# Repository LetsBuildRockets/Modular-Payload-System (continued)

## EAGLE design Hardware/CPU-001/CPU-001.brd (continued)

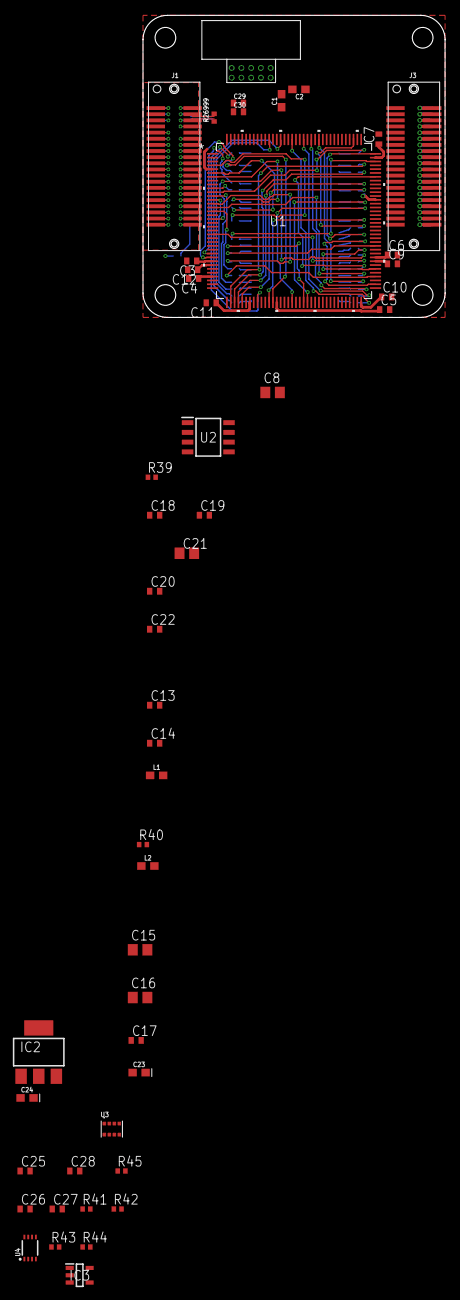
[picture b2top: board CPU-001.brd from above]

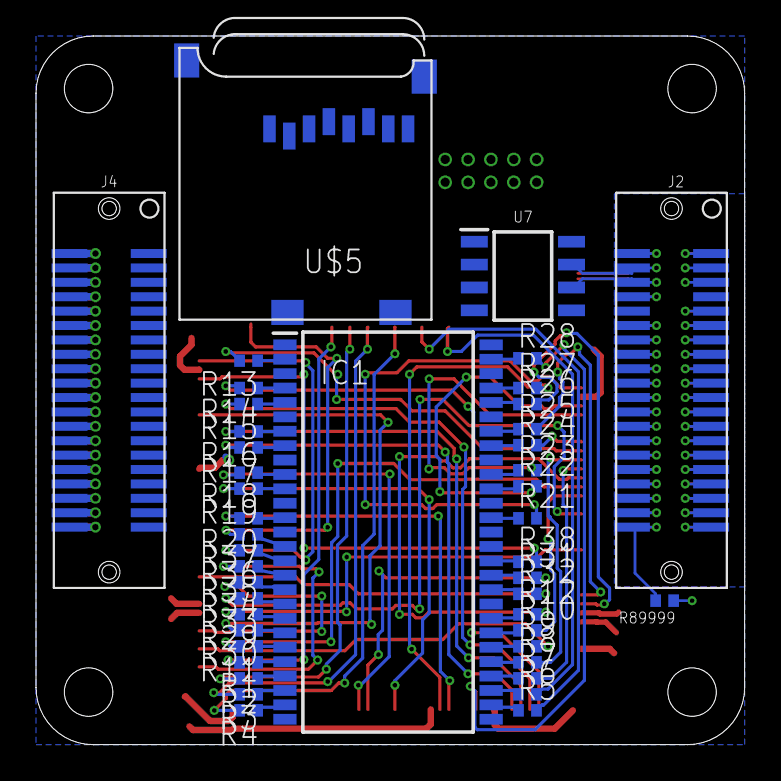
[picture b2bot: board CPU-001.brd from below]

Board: 2 copper layers, 39.4 x 39.4 mm, 93 parts (44 on the bottom side), 135 nets.

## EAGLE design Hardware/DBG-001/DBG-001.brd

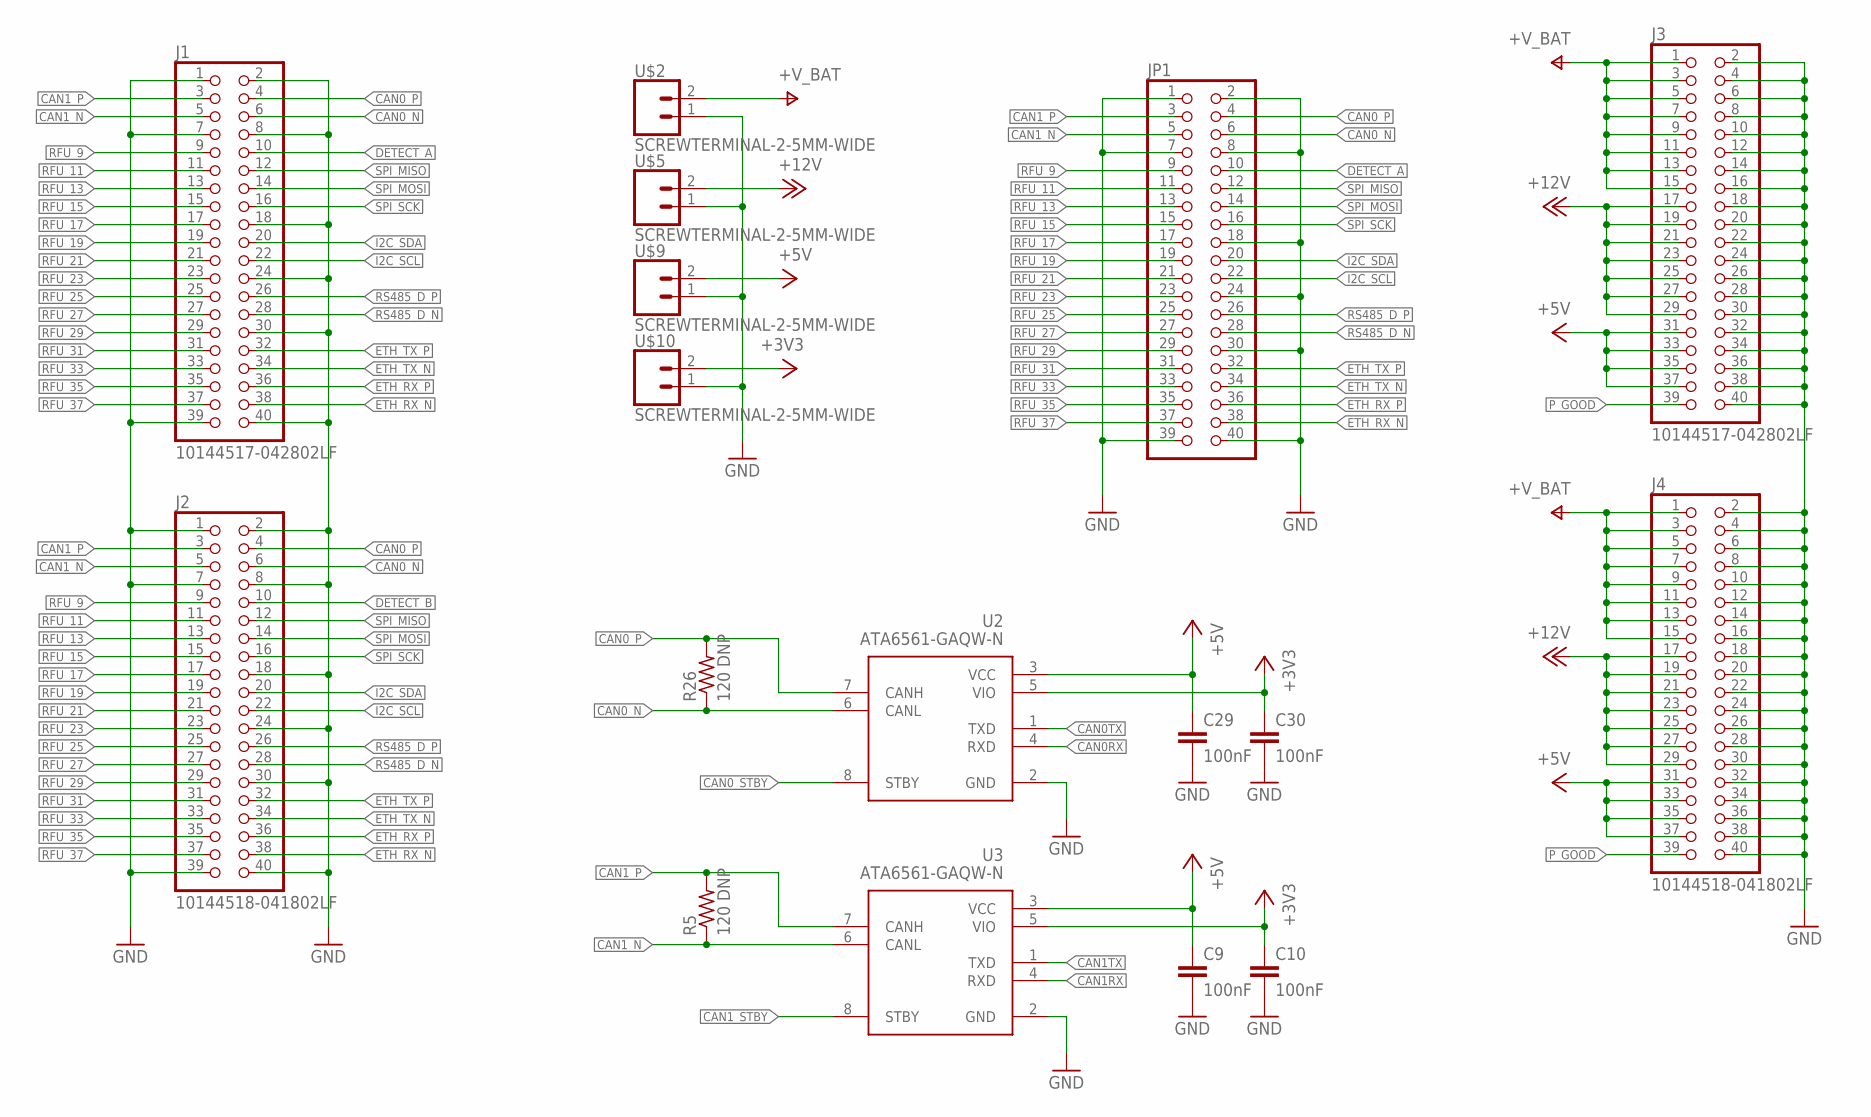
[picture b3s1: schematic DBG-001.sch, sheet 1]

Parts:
C9, C10, C29, C30: 100nF; C0402
J1, J3: 10144517-042802LF
J2, J4: 10144518-041802LF
JP1: PINHD-2X20; 2X20
R5, R26: 120 DNP; R0402
U2, U3: ATA6561-GAQW-N; SOIC127P600X175-8N
U$2, U$5, U$9, U$10: SCREWTERMINAL-2-5MM-WIDE; SCREWTERMINAL-5MM-2-WIDE

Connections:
+3V3: C10.1, C30.1, U2.5 (VIO), U3.5 (VIO), U$10.2; also elsewhere on the board
+5V: C9.1, C29.1, J3.31, J3.33, J3.35, J3.37, J4.31, J4.33, J4.35, J4.37, U2.3 (VCC), U3.3 (VCC), U$9.2; also elsewhere on the board
+12V: J3.17, J3.19, J3.21, J3.23, J3.25, J3.27, J3.29, J4.17, J4.19, J4.21, J4.23, J4.25, J4.27, J4.29, U$5.2
+V_BAT: J3.1, J3.3, J3.5, J3.7, J3.9, J3.11, J3.13, J3.15, J4.1, J4.3, J4.5, J4.7, J4.9, J4.11, J4.13, J4.15, U$2.2
CAN0RX: U2.4 (RXD); also elsewhere on the board
CAN0TX: U2.1 (TXD); also elsewhere on the board
CAN0_N: J1.6, J2.6, JP1.6, R26.1, U2.6 (CANL)
CAN0_P: J1.4, J2.4, JP1.4, R26.2, U2.7 (CANH)
CAN0_STBY: U2.8 (STBY); also elsewhere on the board
CAN1RX: U3.4 (RXD); also elsewhere on the board
CAN1TX: U3.1 (TXD); also elsewhere on the board
CAN1_N: J1.5, J2.5, JP1.5, R5.1, U3.6 (CANL)
CAN1_P: J1.3, J2.3, JP1.3, R5.2, U3.7 (CANH)
CAN1_STBY: U3.8 (STBY); also elsewhere on the board
DETECT_A: J1.10, JP1.10; also elsewhere on the board
DETECT_B: J2.10; also elsewhere on the board
ETH_RX_N: J1.38, J2.38, JP1.38
ETH_RX_P: J1.36, J2.36, JP1.36
ETH_TX_N: J1.34, J2.34, JP1.34
ETH_TX_P: J1.32, J2.32, JP1.32
GND: C9.2, C10.2, C29.2, C30.2, J1.1, J1.2, J1.7, J1.8, J1.18, J1.24, J1.30, J1.39, J1.40, J2.1, J2.2, J2.7, J2.8, J2.18, J2.24, J2.30, J2.39, J2.40, J3.2, J3.4, J3.6, J3.8, J3.10, J3.12, J3.14, J3.16, J3.18, J3.20, J3.22, J3.24, J3.26, J3.28, J3.30, J3.32, J3.34, J3.36, J3.38, J3.40, J4.2, J4.4, J4.6, J4.8, J4.10, J4.12, J4.14, J4.16, J4.18, J4.20, J4.22, J4.24, J4.26, J4.28, J4.30, J4.32, J4.34, J4.36, J4.38, J4.40, JP1.1, JP1.2, JP1.7, JP1.8, JP1.18, JP1.24, JP1.30, JP1.39, JP1.40, U2.2 (GND), U3.2 (GND), U$2.1, U$5.1, U$9.1, U$10.1; also elsewhere on the board
I2C_SCL: J1.22, J2.22, JP1.22; also elsewhere on the board
I2C_SDA: J1.20, J2.20, JP1.20; also elsewhere on the board
P_GOOD: J3.39, J4.39; also elsewhere on the board
RFU_9: J1.9, J2.9, JP1.9
RFU_11: J1.11, J2.11, JP1.11
RFU_13: J1.13, J2.13, JP1.13
RFU_15: J1.15, J2.15, JP1.15
RFU_17: J1.17, J2.17, JP1.17
RFU_19: J1.19, J2.19, JP1.19
RFU_21: J1.21, J2.21, JP1.21
RFU_23: J1.23, J2.23, JP1.23
RFU_25: J1.25, J2.25, JP1.25
RFU_27: J1.27, J2.27, JP1.27
RFU_29: J1.29, J2.29, JP1.29
RFU_31: J1.31, J2.31, JP1.31
RFU_33: J1.33, J2.33, JP1.33
RFU_35: J1.35, J2.35, JP1.35
RFU_37: J1.37, J2.37, JP1.37
RS485_D_N: J1.28, J2.28, JP1.28
RS485_D_P: J1.26, J2.26, JP1.26
SPI_MISO: J1.12, J2.12, JP1.12; also elsewhere on the board
SPI_MOSI: J1.14, J2.14, JP1.14; also elsewhere on the board
SPI_SCK: J1.16, J2.16, JP1.16; also elsewhere on the board

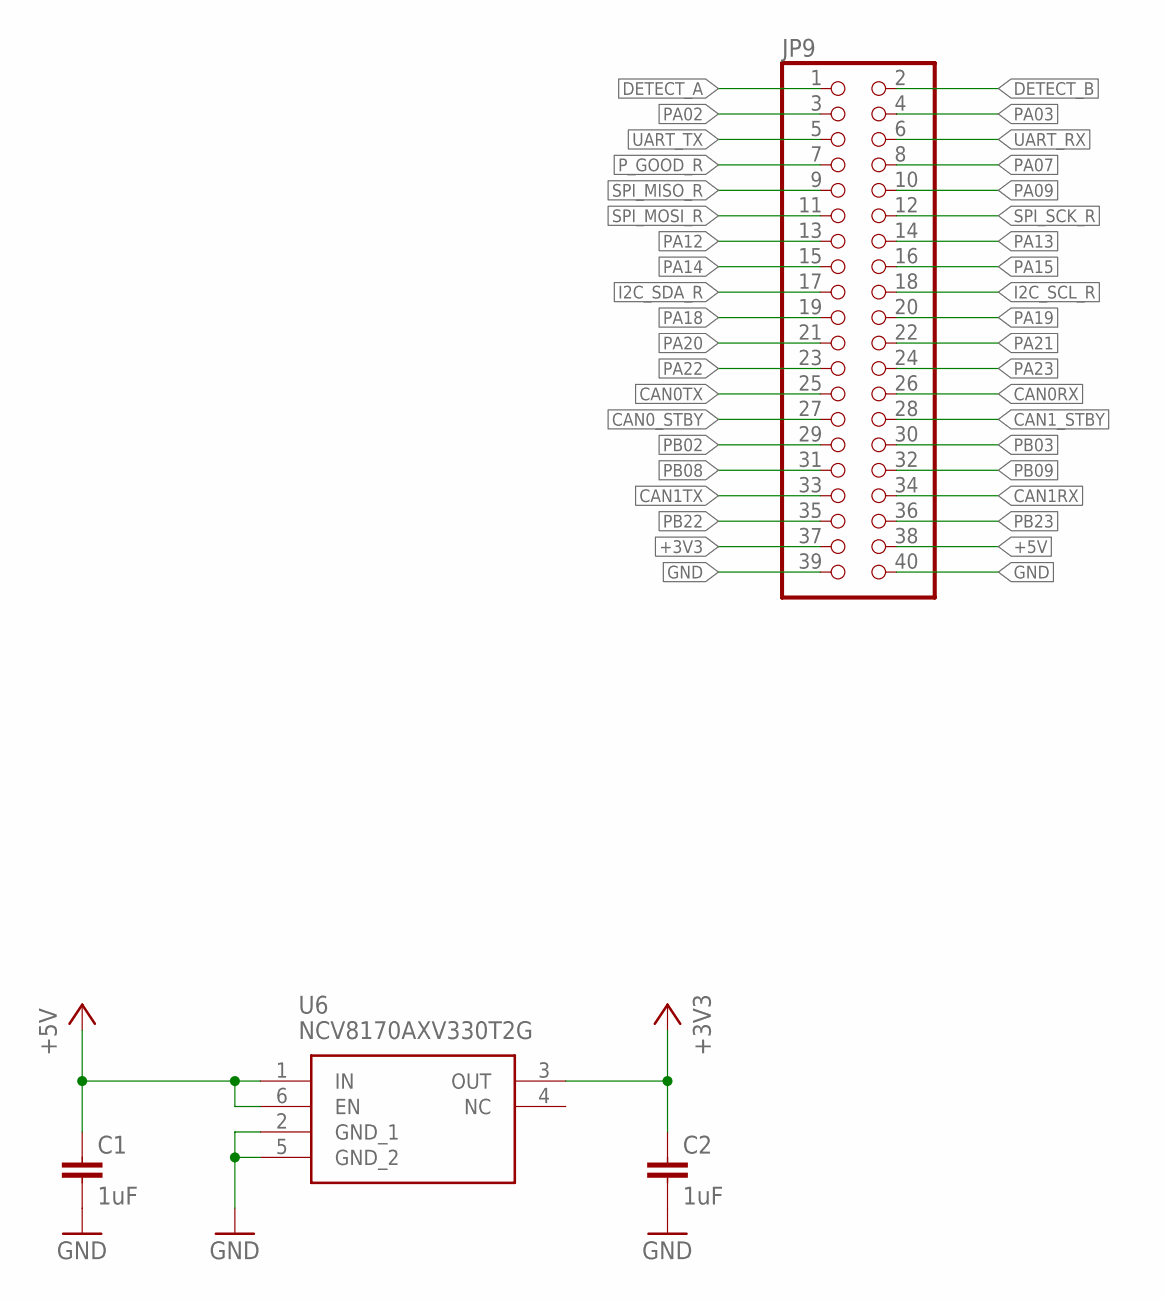
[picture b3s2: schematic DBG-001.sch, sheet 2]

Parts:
C1, C2: 1uF; C0603
JP9: PINHD-2X20; 2X20
U6: NCV8170AXV330T2G; SOTFL50P160X60-6N

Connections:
+3V3: C2.1, JP9.37, U6.3 (OUT); also elsewhere on the board
+5V: C1.1, JP9.38, U6.1 (IN), U6.6 (EN); also elsewhere on the board
CAN0RX: JP9.26; also elsewhere on the board
CAN0TX: JP9.25; also elsewhere on the board
CAN0_STBY: JP9.27; also elsewhere on the board
CAN1RX: JP9.34; also elsewhere on the board
CAN1TX: JP9.33; also elsewhere on the board
CAN1_STBY: JP9.28; also elsewhere on the board
DETECT_A: JP9.1; also elsewhere on the board
DETECT_B: JP9.2; also elsewhere on the board
GND: C1.2, C2.2, JP9.39, JP9.40, U6.2 (GND_1), U6.5 (GND_2); also elsewhere on the board
I2C_SCL_R: JP9.18; also elsewhere on the board
I2C_SDA_R: JP9.17; also elsewhere on the board
PA02: JP9.3; also elsewhere on the board
PA03: JP9.4; also elsewhere on the board
PA07: JP9.8; also elsewhere on the board
PA09: JP9.10; also elsewhere on the board
PA12: JP9.13; also elsewhere on the board
PA13: JP9.14; also elsewhere on the board
PA14: JP9.15; also elsewhere on the board
PA15: JP9.16; also elsewhere on the board
PA18: JP9.19; also elsewhere on the board
PA19: JP9.20; also elsewhere on the board
PA20: JP9.21; also elsewhere on the board
PA21: JP9.22; also elsewhere on the board
PA22: JP9.23; also elsewhere on the board
PA23: JP9.24; also elsewhere on the board
PB02: JP9.29; also elsewhere on the board
PB03: JP9.30; also elsewhere on the board
PB08: JP9.31; also elsewhere on the board
PB09: JP9.32; also elsewhere on the board
PB22: JP9.35; also elsewhere on the board
PB23: JP9.36; also elsewhere on the board
P_GOOD_R: JP9.7; also elsewhere on the board
SPI_MISO_R: JP9.9; also elsewhere on the board
SPI_MOSI_R: JP9.11; also elsewhere on the board
SPI_SCK_R: JP9.12; also elsewhere on the board
UART_RX: JP9.6; also elsewhere on the board
UART_TX: JP9.5; also elsewhere on the board

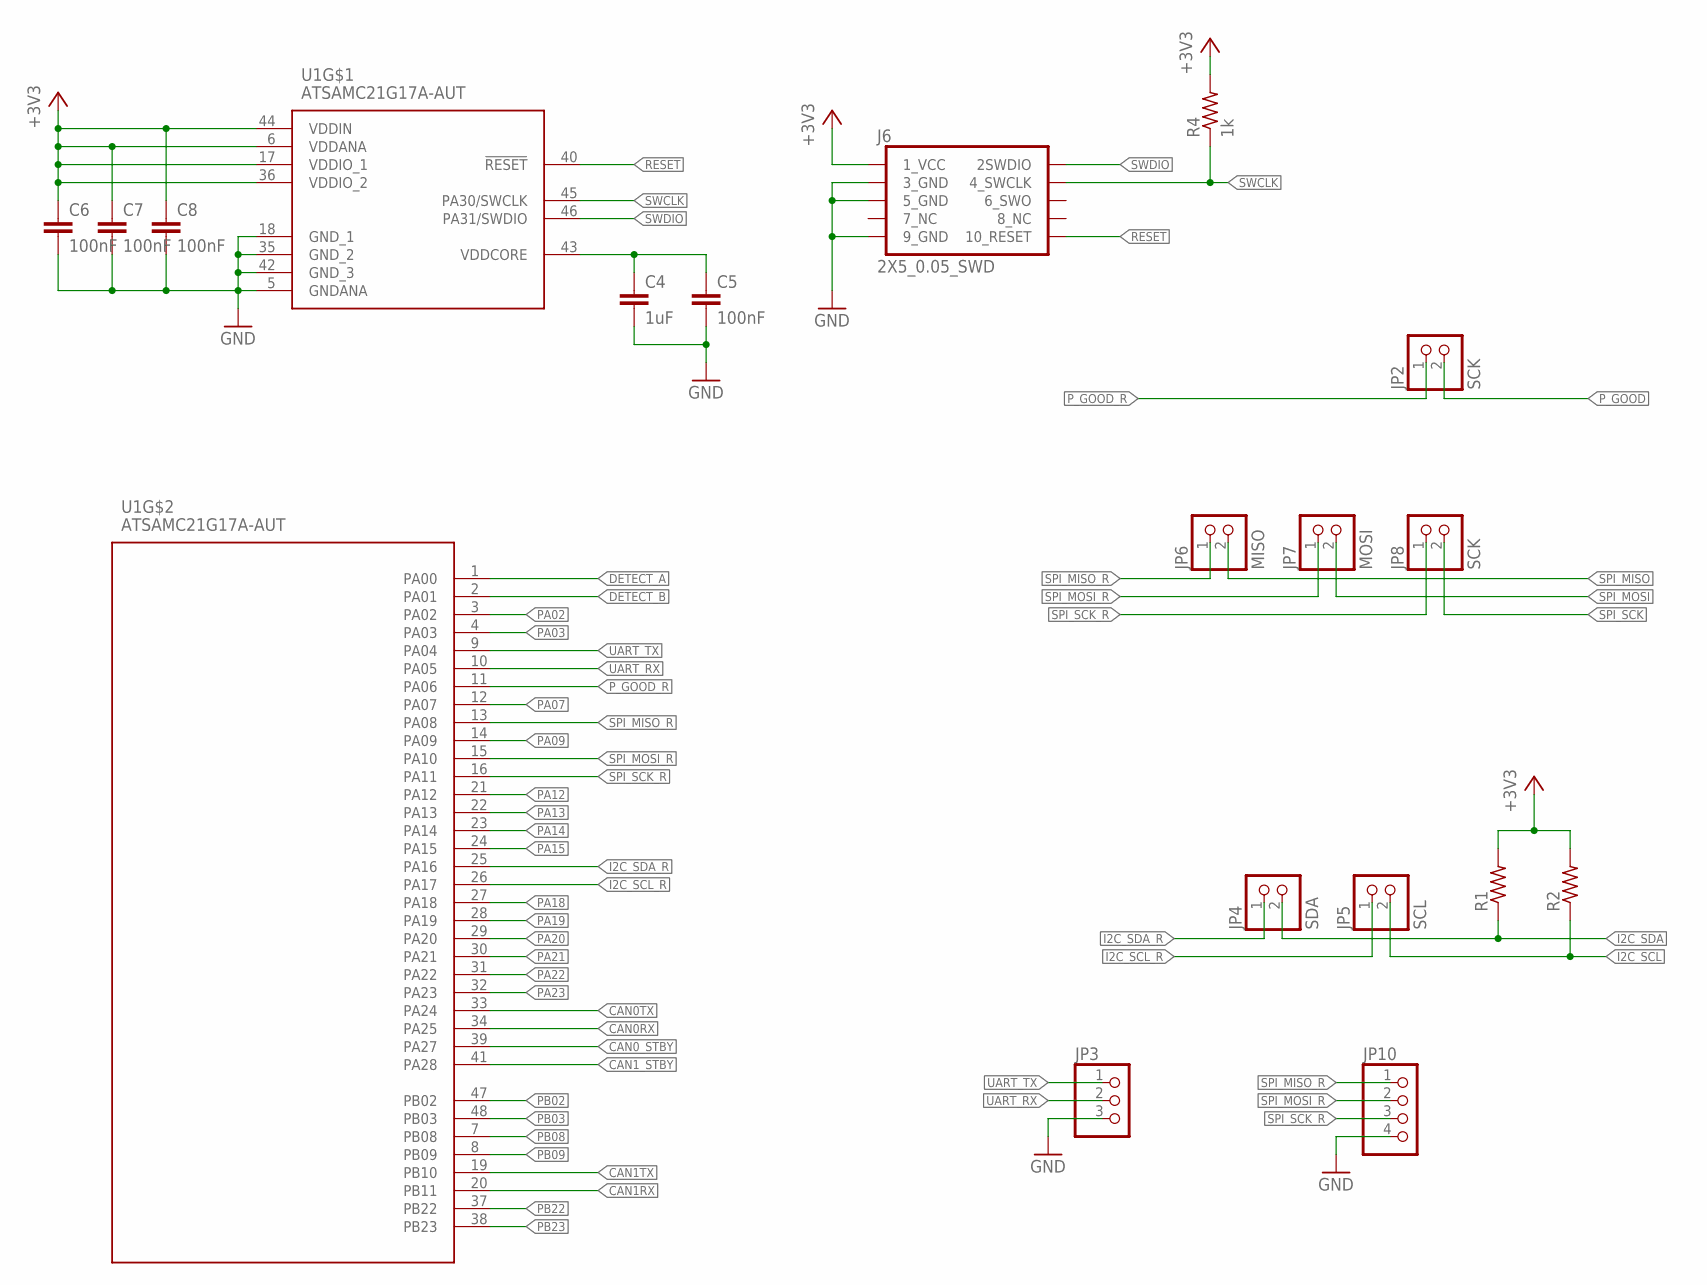
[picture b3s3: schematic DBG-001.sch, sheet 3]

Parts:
C4: 1uF; C0805
C5, C6, C7, C8: 100nF; C0805
J6: 2X5_0.05_SWD; 2X5_RIGHT
JP2, JP8: SCK; 1X02
JP3: PINHD-1X3; 1X03
JP4: SDA; 1X02
JP5: SCL; 1X02
JP6: MISO; 1X02
JP7: MOSI; 1X02
JP10: PINHD-1X4; 1X04
R1, R2: R-US_R0805; R0805
R4: 1k; R0402
U1: ATSAMC21G17A-AUT; QFP50P900X900X120-48N

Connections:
+3V3: C6.1, C7.1, C8.1, J6.1 (1_VCC), R1.2, R2.2, R4.2, U1.6 (VDDANA), U1.17 (VDDIO_1), U1.36 (VDDIO_2), U1.44 (VDDIN); also elsewhere on the board
CAN0RX: U1.34 (PA25); also elsewhere on the board
CAN0TX: U1.33 (PA24); also elsewhere on the board
CAN0_STBY: U1.39 (PA27); also elsewhere on the board
CAN1RX: U1.20 (PB11); also elsewhere on the board
CAN1TX: U1.19 (PB10); also elsewhere on the board
CAN1_STBY: U1.41 (PA28); also elsewhere on the board
DETECT_A: U1.1 (PA00); also elsewhere on the board
DETECT_B: U1.2 (PA01); also elsewhere on the board
GND: C4.2, C5.2, C6.2, C7.2, C8.2, J6.3 (3_GND), J6.5 (5_GND), J6.9 (9_GND), JP3.3, JP10.4, U1.5 (GNDANA), U1.18 (GND_1), U1.35 (GND_2), U1.42 (GND_3); also elsewhere on the board
I2C_SCL: JP5.2, R2.1; also elsewhere on the board
I2C_SCL_R: JP5.1, U1.26 (PA17); also elsewhere on the board
I2C_SDA: JP4.2, R1.1; also elsewhere on the board
I2C_SDA_R: JP4.1, U1.25 (PA16); also elsewhere on the board
unnamed: C4.1, C5.1, U1.43 (VDDCORE)
PA02: U1.3 (PA02); also elsewhere on the board
PA03: U1.4 (PA03); also elsewhere on the board
PA07: U1.12 (PA07); also elsewhere on the board
PA09: U1.14 (PA09); also elsewhere on the board
PA12: U1.21 (PA12); also elsewhere on the board
PA13: U1.22 (PA13); also elsewhere on the board
PA14: U1.23 (PA14); also elsewhere on the board
PA15: U1.24 (PA15); also elsewhere on the board
PA18: U1.27 (PA18); also elsewhere on the board
PA19: U1.28 (PA19); also elsewhere on the board
PA20: U1.29 (PA20); also elsewhere on the board
PA21: U1.30 (PA21); also elsewhere on the board
PA22: U1.31 (PA22); also elsewhere on the board
PA23: U1.32 (PA23); also elsewhere on the board
PB02: U1.47 (PB02); also elsewhere on the board
PB03: U1.48 (PB03); also elsewhere on the board
PB08: U1.7 (PB08); also elsewhere on the board
PB09: U1.8 (PB09); also elsewhere on the board
PB22: U1.37 (PB22); also elsewhere on the board
PB23: U1.38 (PB23); also elsewhere on the board
P_GOOD: JP2.2; also elsewhere on the board
P_GOOD_R: JP2.1, U1.11 (PA06); also elsewhere on the board
RESET: J6.10 (10_RESET), U1.40 (!RESET)
SPI_MISO: JP6.2; also elsewhere on the board
SPI_MISO_R: JP6.1, JP10.1, U1.13 (PA08); also elsewhere on the board
SPI_MOSI: JP7.2; also elsewhere on the board
SPI_MOSI_R: JP7.1, JP10.2, U1.15 (PA10); also elsewhere on the board
SPI_SCK: JP8.2; also elsewhere on the board
SPI_SCK_R: JP8.1, JP10.3, U1.16 (PA11); also elsewhere on the board
SWCLK: J6.4 (4_SWCLK), R4.1, U1.45 (PA30/SWCLK)
SWDIO: J6.2 (2SWDIO), U1.46 (PA31/SWDIO)
UART_RX: JP3.2, U1.10 (PA05); also elsewhere on the board
UART_TX: JP3.1, U1.9 (PA04); also elsewhere on the board

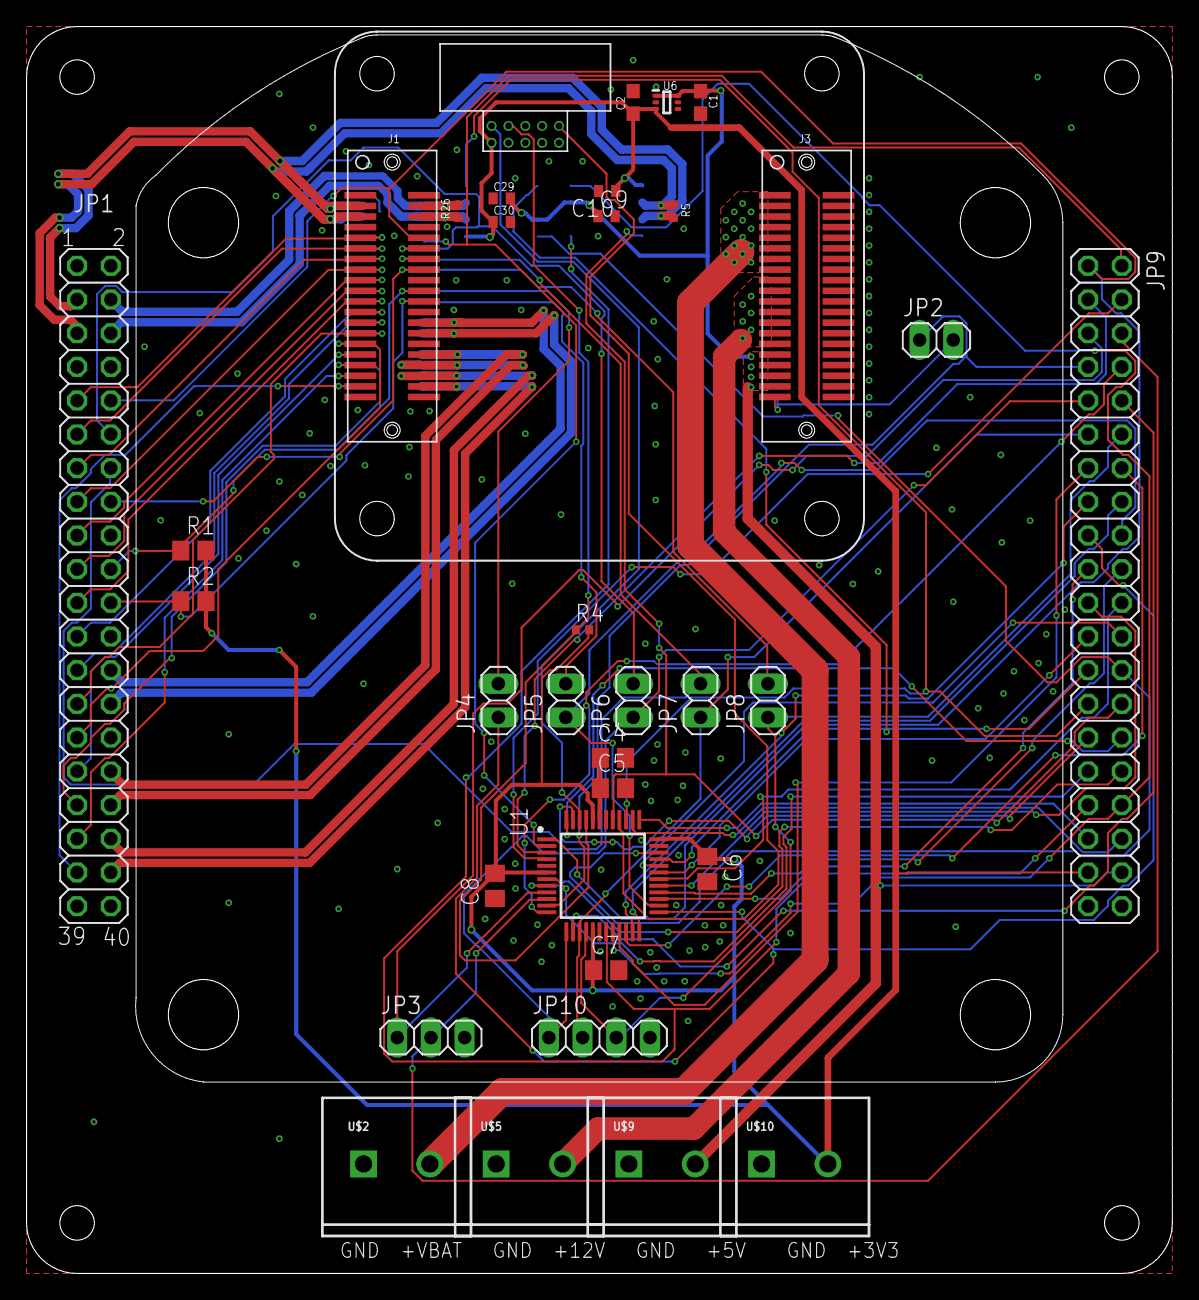
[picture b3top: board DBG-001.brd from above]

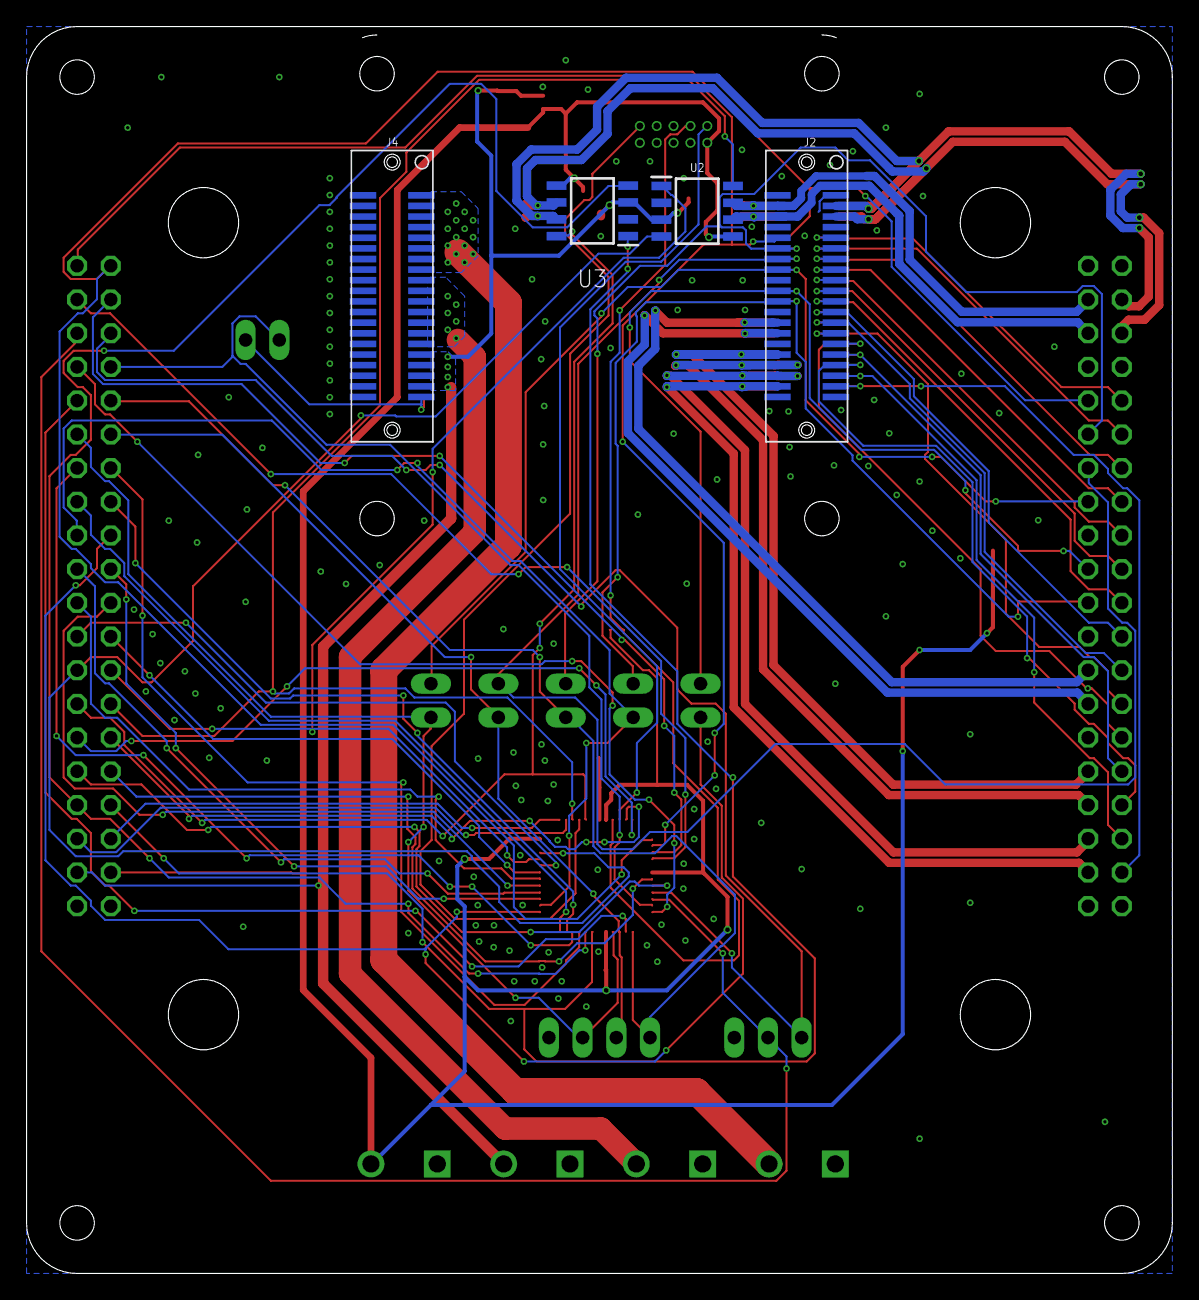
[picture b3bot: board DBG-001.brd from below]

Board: 2 copper layers, 86.4 x 94.0 mm, 39 parts (4 on the bottom side), 76 nets.

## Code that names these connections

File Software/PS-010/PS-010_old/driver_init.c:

/*
 * Code generated from Atmel Start.
 *
 * This file will be overwritten when reconfiguring your Atmel Start project.
 * Please copy examples or other code you want to keep to a separate file
 * to avoid losing it when reconfiguring.
 */

#include "driver_init.h"
#include <peripheral_clk_config.h>
#include <utils.h>
#include <hal_init.h>

#include <hpl_adc_base.h>

struct can_async_descriptor CAN_0;

struct adc_sync_descriptor ADC_0;

struct usart_sync_descriptor DEBUG_UART;

void ADC_0_PORT_init(void)
{

	// Disable digital pin circuitry
	gpio_set_pin_direction(PA02, GPIO_DIRECTION_OFF);

	gpio_set_pin_function(PA02, PINMUX_PA02B_ADC0_AIN0);

	// Disable digital pin circuitry
	gpio_set_pin_direction(PA04, GPIO_DIRECTION_OFF);

	gpio_set_pin_function(PA04, PINMUX_PA04B_ADC0_AIN4);

	// Disable digital pin circuitry
	gpio_set_pin_direction(PA05, GPIO_DIRECTION_OFF);

	gpio_set_pin_function(PA05, PINMUX_PA05B_ADC0_AIN5);

	// Disable digital pin circuitry
	gpio_set_pin_direction(PA06, GPIO_DIRECTION_OFF);

	gpio_set_pin_function(PA06, PINMUX_PA06B_ADC0_AIN6);

	// Disable digital pin circuitry
	gpio_set_pin_direction(PA07, GPIO_DIRECTION_OFF);

	gpio_set_pin_function(PA07, PINMUX_PA07B_ADC0_AIN7);

	// Disable digital pin circuitry
	gpio_set_pin_direction(PA08, GPIO_DIRECTION_OFF);

	gpio_set_pin_function(PA08, PINMUX_PA08B_ADC0_AIN8);

	// Disable digital pin circuitry
	gpio_set_pin_direction(PA09, GPIO_DIRECTION_OFF);

	gpio_set_pin_function(PA09, PINMUX_PA09B_ADC0_AIN9);

	// Disable digital pin circuitry
	gpio_set_pin_direction(PA10, GPIO_DIRECTION_OFF);

	gpio_set_pin_function(PA10, PINMUX_PA10B_ADC0_AIN10);

	// Disable digital pin circuitry
	gpio_set_pin_direction(PA11, GPIO_DIRECTION_OFF);

	gpio_set_pin_function(PA11, PINMUX_PA11B_ADC0_AIN11);

	// Disable digital pin circuitry
	gpio_set_pin_direction(PA03, GPIO_DIRECTION_OFF);

	gpio_set_pin_function(PA03, PINMUX_PA03B_ADC0_VREFP);
}

void ADC_0_CLOCK_init(void)
{
	hri_mclk_set_APBCMASK_ADC0_bit(MCLK);
	hri_gclk_write_PCHCTRL_reg(GCLK, ADC0_GCLK_ID, CONF_GCLK_ADC0_SRC | (1 << GCLK_PCHCTRL_CHEN_Pos));
}

void ADC_0_init(void)
{
	ADC_0_CLOCK_init();
	ADC_0_PORT_init();
	adc_sync_init(&ADC_0, ADC0, _adc_get_adc_sync());
}

void DEBUG_UART_PORT_init(void)
{

	gpio_set_pin_function(PA16, PINMUX_PA16D_SERCOM3_PAD0);

	gpio_set_pin_function(PA17, PINMUX_PA17D_SERCOM3_PAD1);
}

void DEBUG_UART_CLOCK_init(void)
{
	hri_gclk_write_PCHCTRL_reg(GCLK, SERCOM3_GCLK_ID_CORE, CONF_GCLK_SERCOM3_CORE_SRC | (1 << GCLK_PCHCTRL_CHEN_Pos));
	hri_gclk_write_PCHCTRL_reg(GCLK, SERCOM3_GCLK_ID_SLOW, CONF_GCLK_SERCOM3_SLOW_SRC | (1 << GCLK_PCHCTRL_CHEN_Pos));
	hri_mclk_set_APBCMASK_SERCOM3_bit(MCLK);
}

void DEBUG_UART_init(void)
{
	DEBUG_UART_CLOCK_init();
	usart_sync_init(&DEBUG_UART, SERCOM3, (void *)NULL);
	DEBUG_UART_PORT_init();
}

void CAN_0_PORT_init(void)
{

	gpio_set_pin_function(PB23, PINMUX_PB23G_CAN0_RX);

	gpio_set_pin_function(PB22, PINMUX_PB22G_CAN0_TX);
}
/**
 * \brief CAN initialization function
 *
 * Enables CAN peripheral, clocks and initializes CAN driver
 */
void CAN_0_init(void)
{
	hri_mclk_set_AHBMASK_CAN0_bit(MCLK);
	hri_gclk_write_PCHCTRL_reg(GCLK, CAN0_GCLK_ID, CONF_GCLK_CAN0_SRC | (1 << GCLK_PCHCTRL_CHEN_Pos));
	can_async_init(&CAN_0, CAN0);
	CAN_0_PORT_init();
}

void system_init(void)
{
	init_mcu();

	// GPIO on PA00

	// Set pin direction to input
	gpio_set_pin_direction(CTRL_SYNC, GPIO_DIRECTION_IN);

	gpio_set_pin_pull_mode(CTRL_SYNC,
	                       // <y> Pull configuration
	                       // <id> pad_pull_config
	                       // <GPIO_PULL_OFF"> Off
	                       // <GPIO_PULL_UP"> Pull-up
	                       // <GPIO_PULL_DOWN"> Pull-down
	                       GPIO_PULL_DOWN);

	gpio_set_pin_function(CTRL_SYNC, GPIO_PIN_FUNCTION_OFF);

	// GPIO on PA12

	// Set pin direction to input
	gpio_set_pin_direction(DETECT_A, GPIO_DIRECTION_IN);

	gpio_set_pin_pull_mode(DETECT_A,
	                       // <y> Pull configuration
	                       // <id> pad_pull_config
	                       // <GPIO_PULL_OFF"> Off
	                       // <GPIO_PULL_UP"> Pull-up
	                       // <GPIO_PULL_DOWN"> Pull-down
	                       GPIO_PULL_UP);

	gpio_set_pin_function(DETECT_A, GPIO_PIN_FUNCTION_OFF);

	// GPIO on PA13

	// Set pin direction to input
	gpio_set_pin_direction(DETECT_B, GPIO_DIRECTION_IN);

	gpio_set_pin_pull_mode(DETECT_B,
	                       // <y> Pull configuration
	                       // <id> pad_pull_config
	                       // <GPIO_PULL_OFF"> Off
	                       // <GPIO_PULL_UP"> Pull-up
	                       // <GPIO_PULL_DOWN"> Pull-down
	                       GPIO_PULL_UP);

	gpio_set_pin_function(DETECT_B, GPIO_PIN_FUNCTION_OFF);

	// GPIO on PA18

	// Set pin direction to input
	gpio_set_pin_direction(PG_5V_BT, GPIO_DIRECTION_IN);

	gpio_set_pin_pull_mode(PG_5V_BT,
	                       // <y> Pull configuration
	                       // <id> pad_pull_config
	                       // <GPIO_PULL_OFF"> Off
	                       // <GPIO_PULL_UP"> Pull-up
	                       // <GPIO_PULL_DOWN"> Pull-down
	                       GPIO_PULL_OFF);

	gpio_set_pin_function(PG_5V_BT, GPIO_PIN_FUNCTION_OFF);

	// GPIO on PA19

	// Set pin direction to input
	gpio_set_pin_direction(PG_5V, GPIO_DIRECTION_IN);

	gpio_set_pin_pull_mode(PG_5V,
	                       // <y> Pull configuration
	                       // <id> pad_pull_config
	                       // <GPIO_PULL_OFF"> Off
	                       // <GPIO_PULL_UP"> Pull-up
	                       // <GPIO_PULL_DOWN"> Pull-down
	                       GPIO_PULL_OFF);

	gpio_set_pin_function(PG_5V, GPIO_PIN_FUNCTION_OFF);

	// GPIO on PA20

	// Set pin direction to input
	gpio_set_pin_direction(PG_12V, GPIO_DIRECTION_IN);

	gpio_set_pin_pull_mode(PG_12V,
	                       // <y> Pull configuration
	                       // <id> pad_pull_config
	                       // <GPIO_PULL_OFF"> Off
	                       // <GPIO_PULL_UP"> Pull-up
	                       // <GPIO_PULL_DOWN"> Pull-down
	                       GPIO_PULL_OFF);

	gpio_set_pin_function(PG_12V, GPIO_PIN_FUNCTION_OFF);

	// GPIO on PA21

	gpio_set_pin_level(EN_12V,
	                   // <y> Initial level
	                   // <id> pad_initial_level
	                   // <false"> Low
	                   // <true"> High
	                   false);

	// Set pin direction to output
	gpio_set_pin_direction(EN_12V, GPIO_DIRECTION_OUT);

	gpio_set_pin_function(EN_12V, GPIO_PIN_FUNCTION_OFF);

	// GPIO on PA22

	gpio_set_pin_level(EN_5V_BT,
	                   // <y> Initial level
	                   // <id> pad_initial_level
	                   // <false"> Low
	                   // <true"> High
	                   true);

	// Set pin direction to output
	gpio_set_pin_direction(EN_5V_BT, GPIO_DIRECTION_OUT);

	gpio_set_pin_function(EN_5V_BT, GPIO_PIN_FUNCTION_OFF);

	// GPIO on PA23

	gpio_set_pin_level(EN_5V,
	                   // <y> Initial level
	                   // <id> pad_initial_level
	                   // <false"> Low
	                   // <true"> High
	                   false);

	// Set pin direction to output
	gpio_set_pin_direction(EN_5V, GPIO_DIRECTION_OUT);

	gpio_set_pin_function(EN_5V, GPIO_PIN_FUNCTION_OFF);

	// GPIO on PA27

	gpio_set_pin_level(P_GOODn,
	                   // <y> Initial level
	                   // <id> pad_initial_level
	                   // <false"> Low
	                   // <true"> High
	                   true);

	// Set pin direction to output
	gpio_set_pin_direction(P_GOODn, GPIO_DIRECTION_OUT);

	gpio_set_pin_function(P_GOODn, GPIO_PIN_FUNCTION_OFF);

	// GPIO on PA28

	gpio_set_pin_level(CAN0_STBY,
	                   // <y> Initial level
	                   // <id> pad_initial_level
	                   // <false"> Low
	                   // <true"> High
	                   true);

	// Set pin direction to output
	gpio_set_pin_direction(CAN0_STBY, GPIO_DIRECTION_OUT);

	gpio_set_pin_function(CAN0_STBY, GPIO_PIN_FUNCTION_OFF);

	ADC_0_init();

	DEBUG_UART_init();
	CAN_0_init();
}

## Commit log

2020-02-10 added current files
2020-02-10 update processor
2020-02-10 added pin mappings
2020-02-10 added SAMC21 to PS-001 tab of pin mappings
2020-02-10 add PS pin mapping
2020-02-10 more work on CPU-001
2020-02-10 updated sch with atsamC21G - brd needs work
2020-02-12 updating voltage rails, should we get rid of
2020-02-12 added altimeter.. working through schematic slowly...
2020-02-12 added some note to ps-001 sch
2020-02-17 fixed supply ORing
2020-02-17 add template files
2020-02-23 added pullup and swdclk and changed some cap packages
2020-04-29 fixed power rail naming in template and added inventor drawing
2020-04-29 updates to CPU-001 and DBG-001
2020-04-29 updates to IO-001
2020-04-29 added a new debug board designed for pogopins
2020-04-29 updates to ps-001
2020-09-20 create TMP-001 Altium files
2020-09-21 added connectors to library...
2020-09-22 added atsamv71, ATA6561, and IS4516800F symbols, but no footprints yet
2020-09-23 sims and some other stuff...
2020-09-27 added altium-libs submodule
2020-09-28 progess on TMP-001...
2020-09-28 test pcb file
2020-09-28 test 2
2020-09-28 commiting libs
2020-09-28 add some new footprints
2020-09-28 add atsamv7 and ram footprints
2020-10-04 progress on TMP-001. lost some work :(
2020-10-10 working on part placement. sch is done.
2020-10-11 routing the board
2020-10-19 working on routing. still need to fix some rules and polys
2020-10-19 add vbat bootstrap\
2020-10-19 updated outline
2020-10-19 tmp-001 done? i should add a PN/SN to the silk
2020-10-20 added more notes, some P/N silkscreen, and licenseing
2020-10-20 remove obsolete template
2020-11-03 DBG-040 ready for release...
2020-11-03 rebased Altium libs
2020-11-12 spacer board work
2020-11-12 updated submodule with CT3151 banana jacks
2020-11-15 added BNC R/A
2020-11-15 started DBG-010
2020-11-15 fixed name and started current sense board
2020-11-23 added PS-010 sim
2020-11-23 added some new symbols for some parts for PS-010
2020-11-23 cleaned up sim files
2020-11-23 started adding PNs to sim
2020-11-27 simulated +5V and +12V input filters
2020-11-27 progress on PS-010!
2020-12-02 board is looking good so far...
2020-12-04 analogs!
2020-12-04 board is nearing completion, so that's kinda cool
2020-12-05 added Unit Price information and finished routing
2020-12-07 work on BAT-010
2020-12-09 idk. who knows
2020-12-20 removed old files
2020-12-20 working on BUS specs....
2020-12-21 more work on the bus specs
2020-12-21 added source follower buffer to P_GOOD
2020-12-23 added some mech. specs.
2020-12-23 added stack height/standoff info and reexpored pdf
2020-12-25 updated TMP-010
2020-12-25 housekeeping... also changed from B.1 to B... im too lazy to deal with minor revs
2020-12-25 update libs ALitum 21
2020-12-25 added orderable PNs
2020-12-25 adding more spec info... i forgot what exactly
2020-12-25 .. github's MD renderer needs another return...
2020-12-26 updated template to use project params by default
2020-12-26 adding sripts
2020-12-26 added footer to modulelist
2020-12-26 fixed typo
2020-12-26 commint scropts before i lose progress
2020-12-26 added connector specs and created fancy compliance matrix template generator
2020-12-26 vairus template updates
2020-12-26 IO-001 --> IO-010
2020-12-26 wokring on DBG-010
2020-12-31 added DETECT_A/DETECT_B to spec.
2020-12-31 trying to fix MD links
2020-12-31 trying to fix relative img link
2020-12-31 adding additional Specs for bus signals and preboot/bootstrap rails
2020-12-31 fixed formatting in Specs, and now the compliance matrix script can handle links and formatting.
2020-12-31 added pinout tables
2020-12-31 added CTRL_SYNC
2021-01-01 added PPS spec and a basic readme
2021-01-01 tuning up params and improving auto gen module list script
2021-01-01 fixing indets
2021-01-01 DBG-010 breakout connector
2021-01-02 cleaning up old files and starting to port CPU-010 to alitum
2021-01-02 working on ATSAM V71 power and data pinouts
2021-01-02 added ethernet to CPU-010 pinout
2021-01-03 added note about series resistors on 3.3V bus singals and a warning about backpowering the 3.3V rail from P_GOOD
2021-01-04 working on ethernet interface
2021-01-05 adding staking info
2021-01-05 updates to DBG
2021-01-05 added magnetics to libary. The Altium Library Loader seems buggy on Altium 21
2021-01-07 work on CPU-010
2021-01-08 added molex mez connector
2021-01-10 fixed standoffs
2021-01-10 CPU-010 and CPUEX-010 work
2021-01-10 more work on DBG-010
2021-01-11 DBG-010 is about ready to order
2021-01-11 fixed P23 pinout
2021-01-12 added DBG-020 and DBG-030 for pogo pins
2021-01-13 DBG-020 and DBG-030 ready for release:
2021-01-13 updated ModuleList.md with releases
2021-01-13 ready for a pre-release of PS-010.
2021-01-13 update modulelist with releases
2021-01-16 DBG-010 ready for release
2021-04-18 starting on SW
2021-04-27 add INST-drivers for test scripts
2021-04-30 added test for rise of voltage rails
2021-05-01 updates to power test
2022-05-21 work on test bench stuff
